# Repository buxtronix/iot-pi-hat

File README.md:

# IoT Pi i/o Hat

A board providing easy access to USB, power and other ports of
the Raspberry Pi compatible board available from my amateur radio
club, VK2BV.

# Features

 * Provides power via Micro-USB or screw terminals
 * Easy access to USB ports
 * USB ports are powered directly, not via the Pi board
 * A/V pins broken out
 * Extra header pins for connecting to the GPIO pins

# BoM

| Description + link | Unit price (AUD) |
| ------------------ | ------------ |
| PCB (any Fab house)|  ~ $1 |
| [Dual USB socket](https://au.rs-online.com/web/p/usb-connectors/8006848/)    | $2.34        |
| or 2x[Single USB socket](https://au.rs-online.com/web/p/usb-connectors/1612306/)    | $1.12        |
| [Micro USB socket](https://au.rs-online.com/web/p/usb-connectors/7025475/) | $1.85 |
| [Polyfuse](https://au.rs-online.com/web/p/resettable-surface-mount-fuses/6478409/) | $0.42 |
| [3.5mm jack](https://au.rs-online.com/web/p/jack-plugs-sockets/8051668/) | $2.06 |
| 5mm screw terminal | ~ $0.40 |
| PCB header strips | ~ $0.40 |

# Schematic

See [iot-board-hat.pdf](https://raw.githubusercontent.com/buxtronix/iot-pi-hat/master/iot-board-hat.pdf)

# Assembly

Assembly is quite straight forward, see the [pictures](images/) for views
of where the parts fit.

The bottom of the board contains the female headers, all other parts are
on the top. Ensure the 28-pin header goes against the board edge (J1/Pi),
not the other 28-pin spot which is available for expansion use.

The board allows for either one dual-usb socket to be mounted, or two
single-usb sockets to be mounted. The latter is useful if using both USB
ports and physical spacing necessitates. See [this image](images/render-4.jpg)
for how the dual-socket version looks.

# Usage

Power is supplied either via the screw terminals, or the micro-USB
connector. For (semi-)permanent installtion, the screw terminals are
recommended as Micro-USB can be less reliable. Be sure to supply only
5v as there is no regulator, nor is there polarity protection.

The poly-fuse protects against overcurrent draw from USB peripherals. If
the fuse is problematic (eg too much voltage drop) you can bypass it by
soldering a bridge across JP1.

The A/V jack follows the connectivity standard per the RPi3+ as well as many
TRRS cables. [See details](https://www.raspberrypi-spy.co.uk/2014/07/raspberry-pi-model-b-3-5mm-audiovideo-jack/)

# Contact

Ben Buxton (bbuxton@gmail.com)

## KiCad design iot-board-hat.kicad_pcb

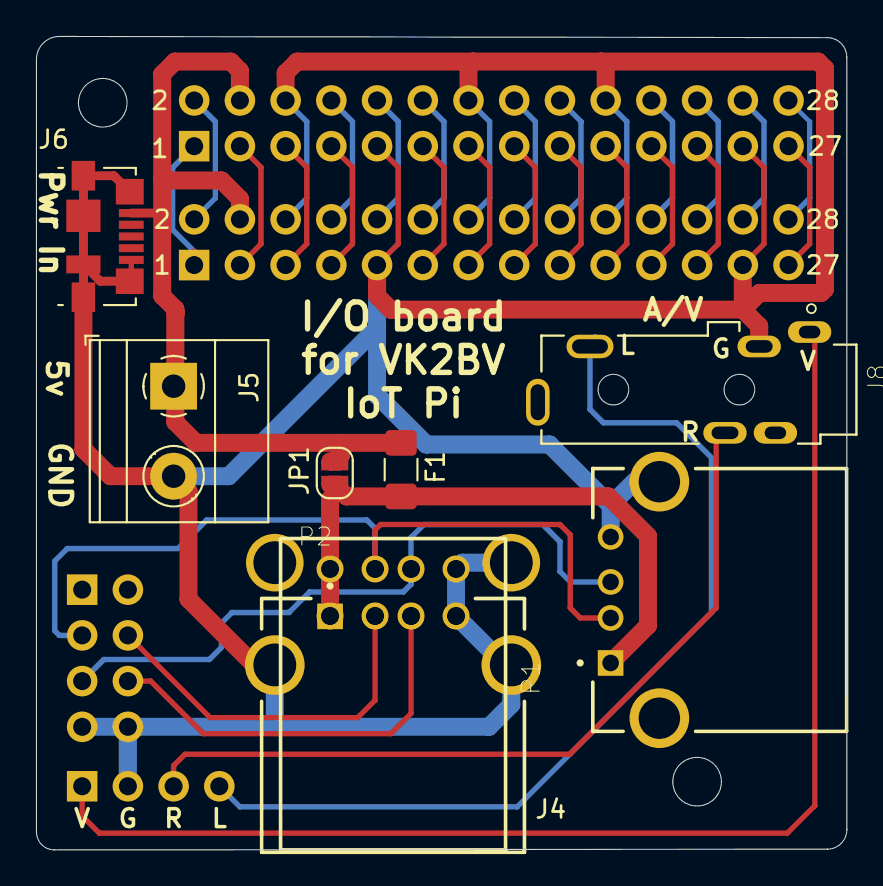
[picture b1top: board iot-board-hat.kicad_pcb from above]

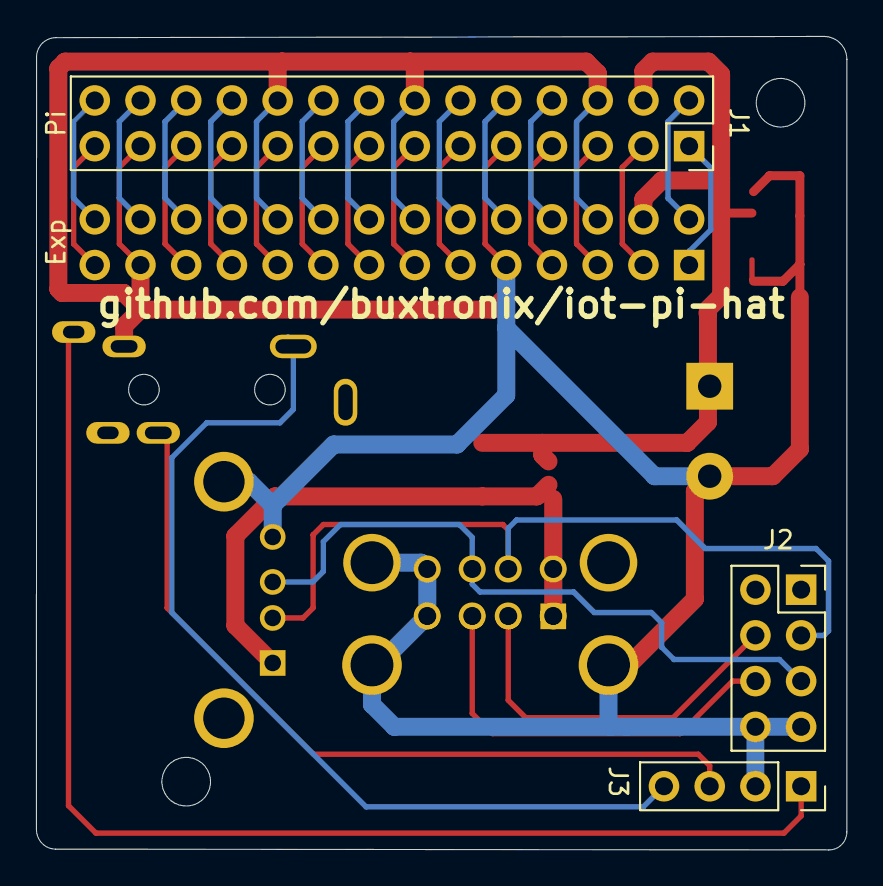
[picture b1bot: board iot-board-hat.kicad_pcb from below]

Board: 2 copper layers, 45.0 x 45.2 mm, 14 parts (4 on the bottom side), 32 nets.

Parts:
F1: Polyfuse; Fuse_1206_3216Metric_Pad1.42x1.75mm_HandSolder
H1, H2: MountingHole; MountingHole_2.7mm_M2.5_ISO7380
J1, J7: Conn_02x14_Odd_Even; PinSocket_2x14_P2.54mm_Vertical
J2: Conn_02x04_Counter_Clockwise; PinSocket_2x04_P2.54mm_Vertical
J3: Conn_01x04; PinSocket_1x04_P2.54mm_Vertical
J4: 67298-3090; MOLEX-DUALUSB
J5: Screw_Terminal_01x02; TerminalBlock_Phoenix_MKDS-1,5-2_1x02_P5.00mm_Horizontal
J6: USB_B_Micro; USB_Micro-B_Molex_47346-0001
J8: FC68127; CLIFF_FC68127
JP1: SolderJumper_2_Open; SolderJumper-2_P1.3mm_Open_RoundedPad1.0x1.5mm
P1, P2: 87520-0010BLF; SAMTEC_USB-A-S-X-X-TH

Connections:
+5F: F1.1, J4.1, J4.5, JP1.2, P1.01, P2.01
+5V: F1.2, J1.4, J5.1, J6.1, J7.4, JP1.1
/a1: J1.1, J7.1
/a2: J1.2, J7.2
/a3: J1.3, J7.3
/a5: J1.5, J7.5
/a7: J1.7, J7.7
/a8: J1.8, J7.8
/a10: J1.10, J7.10
/a11: J1.11, J7.11
/a12: J1.12, J7.12
/a13: J1.13, J7.13
/a15: J1.15, J7.15
/a16: J1.16, J7.16
/a17: J1.17, J7.17
/a18: J1.18, J7.18
/a19: J1.19, J7.19
/a21: J1.21, J7.21
/a22: J1.22, J7.22
/a23: J1.23, J7.23
/a24: J1.24, J7.24
/a26: J1.26, J7.26
/a27: J1.27, J7.27
/a28: J1.28, J7.28
/a-l: J3.4, J8.3
/a-r: J3.3, J8.2
/c-vid: J3.1, J8.1
GND: J1.6, J1.9, J1.14, J1.20, J1.25, J2.7, J2.8, J3.2, J4.4, J4.8, J4.10, J4.11, J4.12, J5.2, J6.5, J6.6, J7.6, J7.9, J7.14, J7.20, J7.25, J8.6, P1.04, P1.S1, P1.S2, P2.04, P2.S1, P2.S2
USB1+: J2.6, J4.3, P2.03
USB1-: J2.4, J4.2, P2.02
USB2+: J2.5, J4.7, P1.03
USB2-: J2.3, J4.6, P1.02

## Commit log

2021-05-31 add images
2021-05-31 fix image
2021-05-31 add schematic pdf
2021-05-31 some tweaks
2021-06-04 Various updates/tweaks
2021-06-16 Version with alternate USB ports
2021-06-16 fix render link
2021-06-16 fix power line
